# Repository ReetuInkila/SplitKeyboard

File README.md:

# SplitKeyboard
A split ergo linear keyboard inspired by [TweetyDaBird/Lotus-Keyboard](https://github.com/TweetyDaBird/Lotus-Keyboard).

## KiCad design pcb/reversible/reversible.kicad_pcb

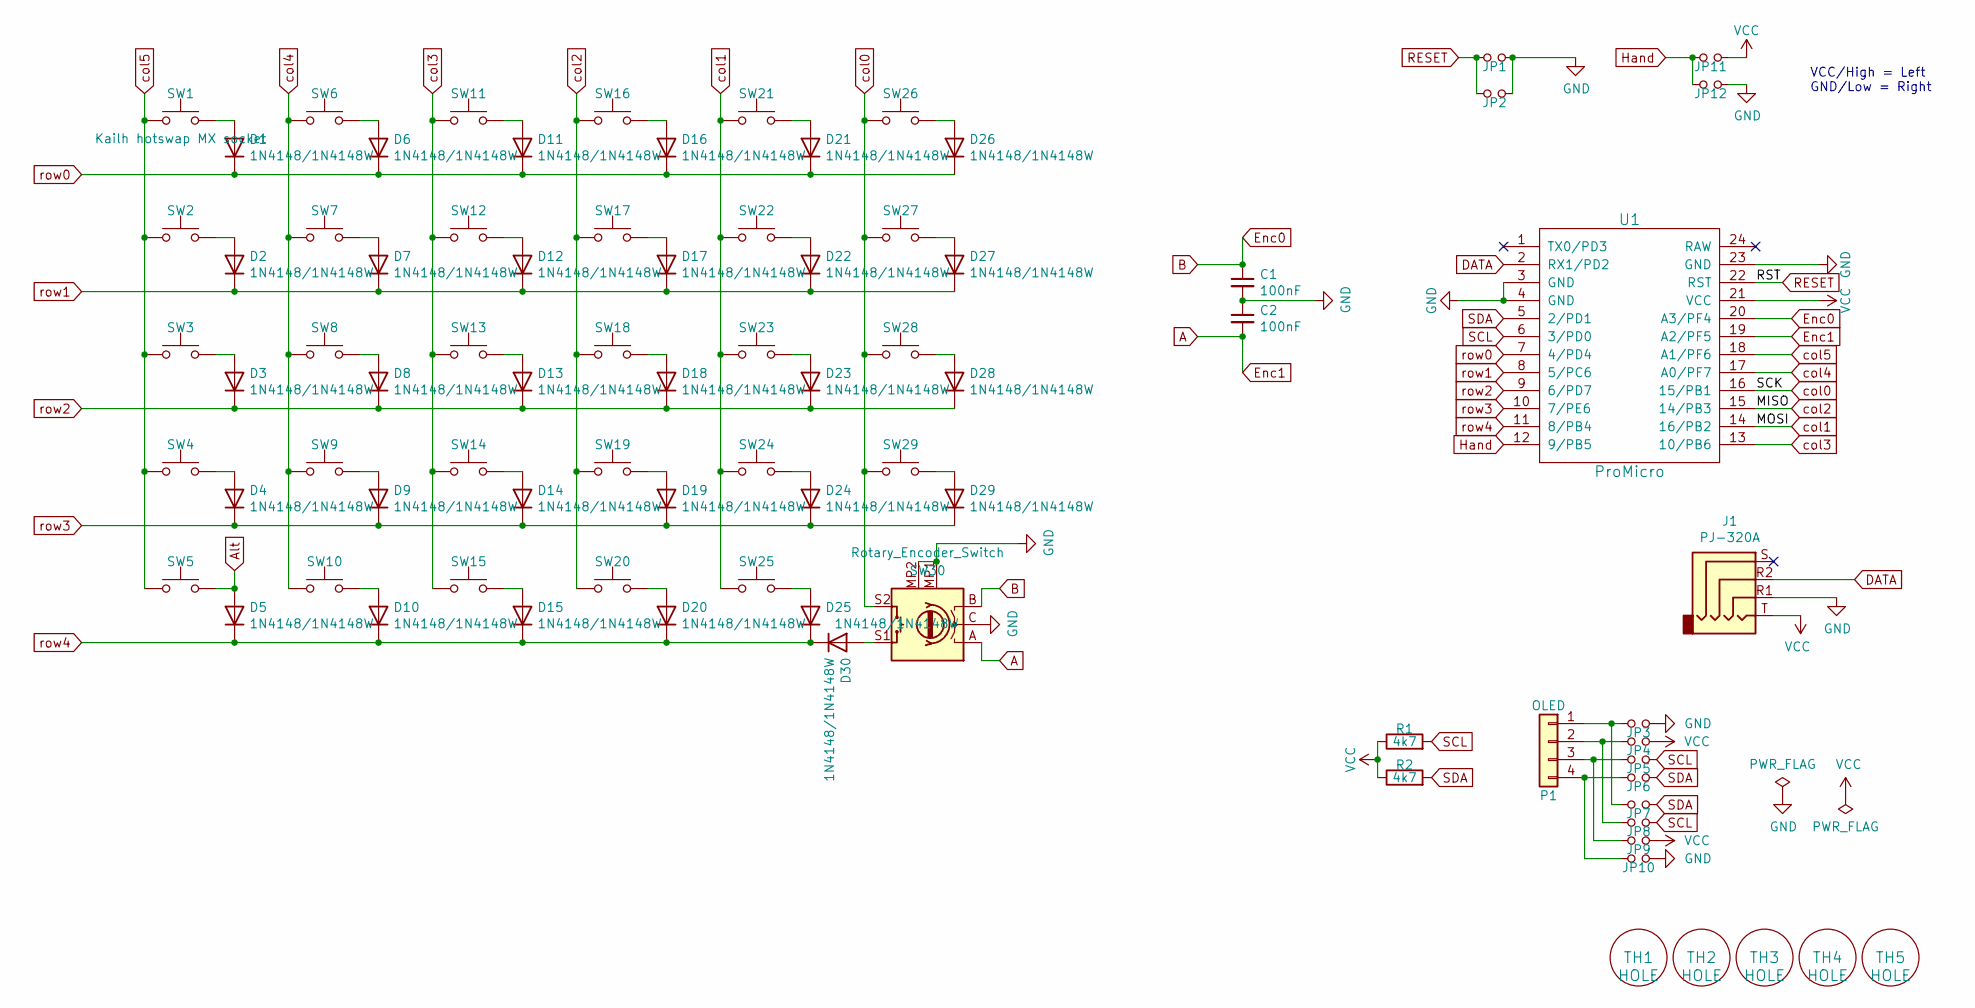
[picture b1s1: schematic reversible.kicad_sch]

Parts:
C1, C2: 100nF; RESISTOR
D1, D2, D3, D4, D5, D6, D7, D8, D9, D10, D11, D12, D13, D14, D15, D16, D17, D18, D19, D20, D21, D22, D23, D24, D25, D26, D27, D28, D29, D30: 1N4148/1N4148W; Diode_TH_SOD123
J1: PJ-320A; TRRS_JACK_MJ4PP9
JP1, JP2: RESET; Jumper
JP3, JP4, JP5, JP6, JP7, JP8, JP9, JP10: Jumper_NO_Small; Jumper
JP11: LEFT; Jumper
JP12: RIGHT; Jumper
P1: OLED; OLED_4Pin
R1, R2: 4k7; R_Axial_DIN0207_L6.3mm_D2.5mm_P7.62mm_Horizontal
SW1, SW2, SW3, SW4, SW5, SW6, SW7, SW8, SW9, SW10, SW11, SW12, SW13, SW14, SW15, SW16, SW17, SW18, SW19, SW20, SW21, SW22, SW23, SW24, SW25, SW26, SW27, SW28, SW29: Kailh hotswap MX socket; Gateron_Low_Profile_Socket
SW30: Rotary_Encoder_Switch; RotaryEncoder_Alps_EC12E-Switch_Vertical_H20mm
TH1, TH2, TH3, TH4, TH5: HOLE; MountingHole_3.7mm
U1: ProMicro; ProMicro_rev2

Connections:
A: C2.2, SW30.A, U1.19 (A2/PF5)
Alt: D5.2 (A), SW5.2
B: C1.1, SW30.B, U1.20 (A3/PF4)
DATA: J1.R2, U1.2 (RX1/PD2)
GND: C1.2, C2.1, J1.R1, JP1.2, JP2.2, JP3.2, JP10.2, JP12.2, SW30.C, SW30.MP1 (GND), SW30.MP2 (GND), U1.3 (GND), U1.4 (GND), U1.23 (GND)
Hand: JP11.1, JP12.1, U1.12 (9/PB5)
unnamed: D1.2 (A), SW1.2
unnamed: D2.2 (A), SW2.2
unnamed: D3.2 (A), SW3.2
unnamed: D4.2 (A), SW4.2
unnamed: D6.2 (A), SW6.2
unnamed: D7.2 (A), SW7.2
unnamed: D8.2 (A), SW8.2
unnamed: D9.2 (A), SW9.2
unnamed: D10.2 (A), SW10.2
unnamed: D11.2 (A), SW11.2
unnamed: D12.2 (A), SW12.2
unnamed: D13.2 (A), SW13.2
unnamed: D14.2 (A), SW14.2
unnamed: D15.2 (A), SW15.2
unnamed: D16.2 (A), SW16.2
unnamed: D17.2 (A), SW17.2
unnamed: D18.2 (A), SW18.2
unnamed: D19.2 (A), SW19.2
unnamed: D20.2 (A), SW20.2
unnamed: D21.2 (A), SW21.2
unnamed: D22.2 (A), SW22.2
unnamed: D23.2 (A), SW23.2
unnamed: D24.2 (A), SW24.2
unnamed: D25.2 (A), SW25.2
unnamed: D26.2 (A), SW26.2
unnamed: D27.2 (A), SW27.2
unnamed: D28.2 (A), SW28.2
unnamed: D29.2 (A), SW29.2
unnamed: D30.2 (A), SW30.S1
unnamed: JP3.1, JP7.1, P1.1
unnamed: JP4.1, JP8.1, P1.2
unnamed: JP5.1, JP9.1, P1.3
unnamed: JP6.1, JP10.1, P1.4
RESET: JP1.1, JP2.1, U1.22 (RST)
SCL: JP5.2, JP8.2, R1.2, U1.6 (3/PD0)
SDA: JP6.2, JP7.2, R2.2, U1.5 (2/PD1)
VCC: J1.T, JP4.2, JP9.2, JP11.2, R1.1, R2.1, U1.21 (VCC)
col0: SW26.1, SW27.1, SW28.1, SW29.1, SW30.S2, U1.16 (15/PB1)
col1: SW21.1, SW22.1, SW23.1, SW24.1, SW25.1, U1.14 (16/PB2)
col2: SW16.1, SW17.1, SW18.1, SW19.1, SW20.1, U1.15 (14/PB3)
col3: SW11.1, SW12.1, SW13.1, SW14.1, SW15.1, U1.13 (10/PB6)
col4: SW6.1, SW7.1, SW8.1, SW9.1, SW10.1, U1.17 (A0/PF7)
col5: SW1.1, SW2.1, SW3.1, SW4.1, SW5.1, U1.18 (A1/PF6)
row0: D1.1 (K), D6.1 (K), D11.1 (K), D16.1 (K), D21.1 (K), D26.1 (K), U1.7 (4/PD4)
row1: D2.1 (K), D7.1 (K), D12.1 (K), D17.1 (K), D22.1 (K), D27.1 (K), U1.8 (5/PC6)
row2: D3.1 (K), D8.1 (K), D13.1 (K), D18.1 (K), D23.1 (K), D28.1 (K), U1.9 (6/PD7)
row3: D4.1 (K), D9.1 (K), D14.1 (K), D19.1 (K), D24.1 (K), D29.1 (K), U1.10 (7/PE6)
row4: D5.1 (K), D10.1 (K), D15.1 (K), D20.1 (K), D25.1 (K), D30.1 (K), U1.11 (8/PB4)

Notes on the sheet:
VCC/High = Left GND/Low = Right

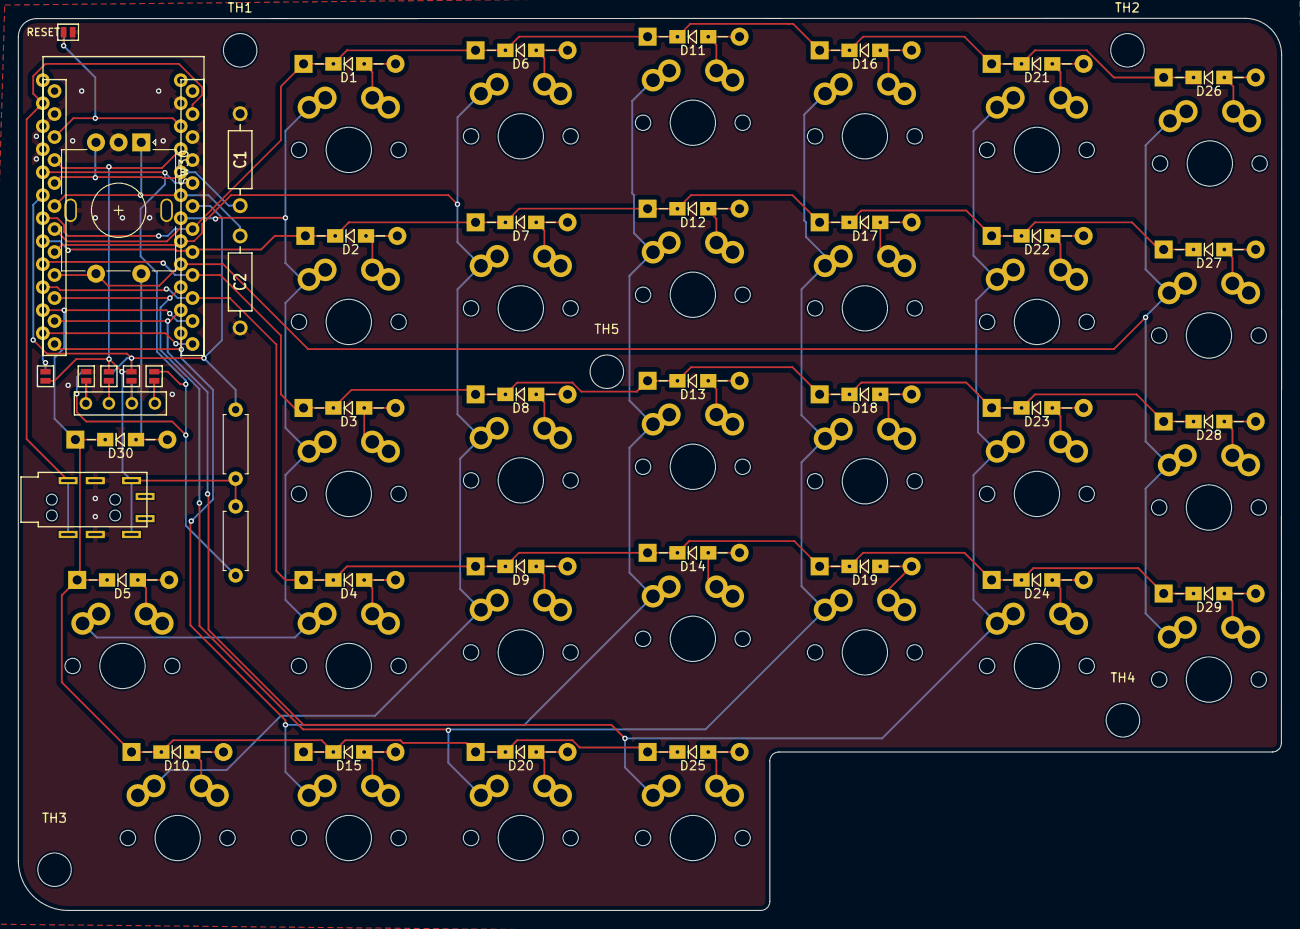
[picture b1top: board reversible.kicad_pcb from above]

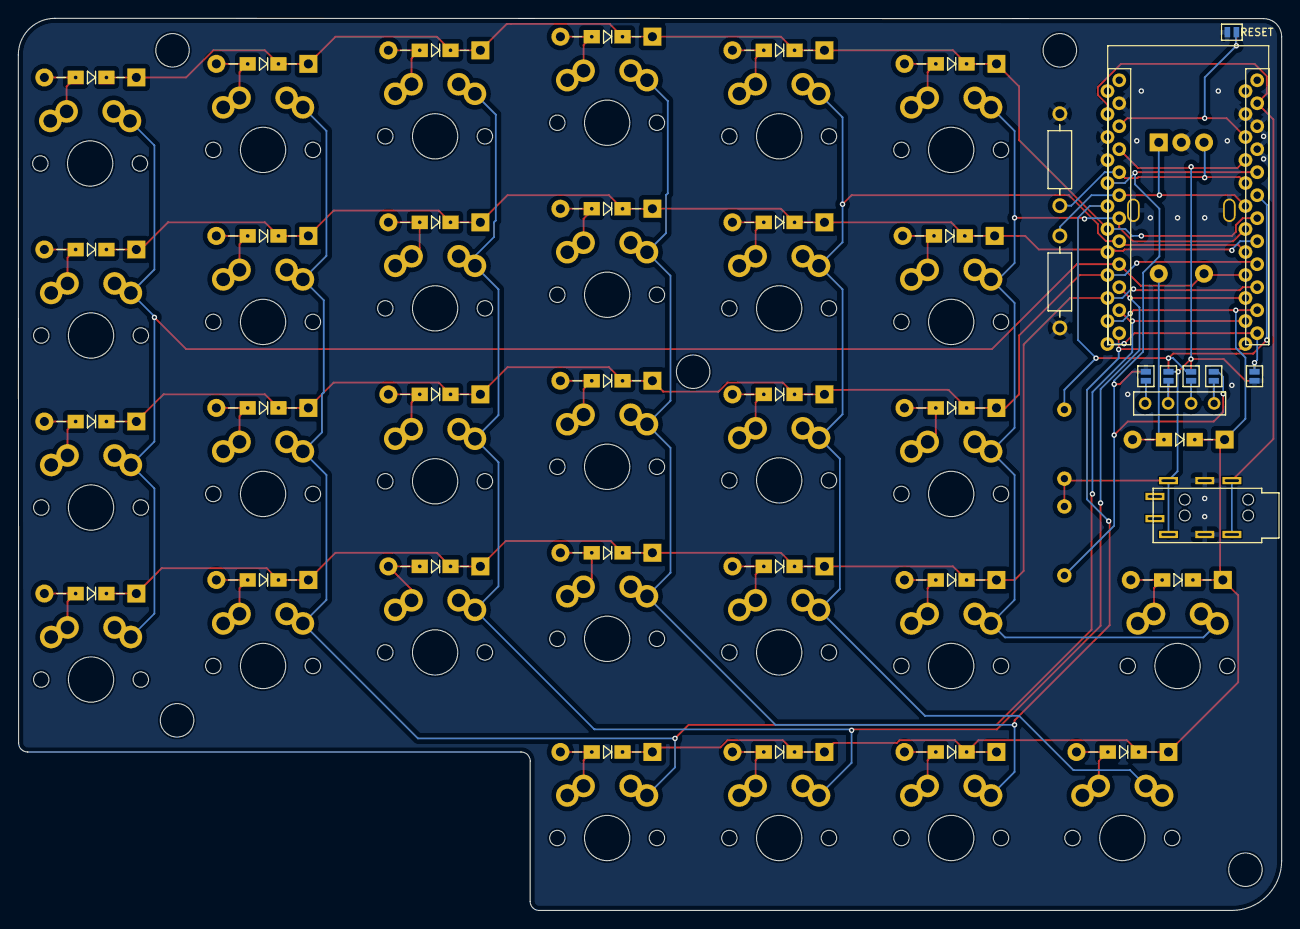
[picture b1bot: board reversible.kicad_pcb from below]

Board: 2 copper layers, 139.5 x 98.5 mm, 84 parts (6 on the bottom side), 54 nets.

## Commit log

2024-02-28 Create LICENSE
2024-02-28 Left pcb project started)
2024-02-28 footprints added
2024-02-28 library footprint library
2024-02-28 righthand pcb project
2024-03-05 started reversible pcb project
2024-03-07 layout designed
2024-03-07 matrix routed
2024-03-08 fixed missing GND connections
2024-03-08 gerber files
